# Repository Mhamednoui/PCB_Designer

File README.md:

# PCB workspace - start here

AI-assisted PCB design with KiCad. This file is the front door: it tells you which other file to
open for what you're trying to do. Don't read everything - jump to the row that matches your task.

| I want to... | Read |
|---|---|
| Understand the environment, installed tools, and what's set up | `CLAUDE.md` (auto-loaded every session) |
| See what MCP servers / Python tools / KiCad plugins exist and how to run them | `docs/TOOLING.md` |
| Build a **new** PCB project from scratch | `docs/NEW_BOARD_PLAYBOOK.md` - the **A-to-Z checklist** - then `docs/PCB_CREATION_GUIDE.md` (the tested procedure) |
| **A build failed and I need the fix** | `docs/PCB_CREATION_GUIDE.md` § "Failure catalogue" |
| Avoid mistakes already made once (KiCad 10 scripting traps, Freerouting quirks) | `docs/LESSONS_LEARNED.md` |
| Work on an **existing** project | that project's own `README.md` under `projects/<name>/` |
| **Order a board** (what the fab / price calculator asks) | that project's `MANUFACTURING.md` |
| **Check the connections without reading a PCB** | that project's `CONNECTIONS.md` - every pin, in words |
| View any board's real 3D layout + inputs/outputs in a browser | `webview/README.md` |
| **See the whole thing at a glance (pictures)** | `docs/diagrams/` — `workflow.svg`, `architecture.svg`, `status.svg` |
| **Actually run the scripts** (commands, stages, which Python) | "Running the scripts" below |

## Running the scripts

**One command does everything** (this is the normal path):
```bash
python pipeline.py uno-toggle            # full build: schematic -> place -> route -> checks -> fab files
python pipeline.py uno-toggle --list     # show which stages would run, change nothing
python pipeline.py uno-toggle --only place,route
python pipeline.py uno-toggle --skip route
```
Stages run in this order, and any that don't apply to a project are skipped automatically:

| Stage | What it does |
|---|---|
| `lint` | Design-rule lint of netlist.py (decoupling, polarity, LED resistors, shorts, pad/pin existence, registry use). Pure Python, <1 s. |
| `parts` | Registry parts vs live/cached LCSC + EasyEDA: MPN, footprint geometry, package, stock, freshness. |
| `sch` | Generate the schematic from netlist.py. |
| `sch-check` | Netlist compare (kicad-cli export vs netlist.py) plus ERC. |
| `place` | Footprints, board outline, silkscreen and pre-routed links. |
| `route` | Autoroute with Freerouting. |
| `finish` | Ground pours and stitching vias. |
| `check` | DRC including schematic parity - the gate before fab. |
| `ir` | Design IR (out/design.json): parts, nets, board geometry from netlist.py + .kicad_pcb; netlist-vs-board net cross-check; JSON-Schema validated. |
| `electrical` | Electrical rules EL-ABSMAX / EL-CONTENTION / EL-OD-PULLUP over out/design.json (runs after `ir`; NOT_JUDGED shown, never fails a hand board). |
| `review` | Design review (kicad-happy schematic/PCB/EMC analyzers + waivers.json): decoupling distance, EMC, power tree. |
| `outputs` | Gerbers, drill, BOM, CPL, STEP, schematic PDF and renders. |
| `lvs` | Independent connectivity of the fab zip itself (gerbers + drill), diffed against netlist.py. |
| `fabreport` | MANUFACTURING.md: size, layers, holes, parts, order-form answers. Read-only on the board. |
| `connections` | CONNECTIONS.md: every pin of every part and where its copper goes, in plain words. |
| `pinmap` | Firmware pin map vs netlist cross-check (enabled by a FIRMWARE block in netlist.py). |
| `spice` | Transient LTspice run of the whole board plus expected-vs-measured (enabled by a SPICE block in netlist.py). |
| `webview` | Export GLB, cache icons, build manifest, onboard to the viewer (works for any .kicad_pcb). |

Useful flags and checks: `--no-cache` (ignore the stage cache), `--describe <stage>`, `--explain RULE-ID`.
Each run writes a report to `projects/<id>/out/run/<ts>/report.html`.
```bash
python tools/ci_checks.py all
python tests/mutations/run_mutations.py --tier fast --jobs 4
python tools/parts.py            # parts registry CLI
```

`pipeline.py` **refuses to re-run design stages on a board that already has `out/fab`** — pass
`--force` if you really mean to rebuild a board that has been sent to fab.

**If you run a script directly, use KiCad's Python, not the system one:**
```bash
"C:\Program Files\KiCad\10.0\bin\python.exe" make_pcb.py place
```
Everything touching `pcbnew` (`make_sch.py`, `check_sch.py`, `make_pcb.py`, `make_outputs.py`) only
imports inside KiCad's interpreter. System `python` gives `ModuleNotFoundError: No module named
'pcbnew'`. `pipeline.py` itself runs under system Python and picks the right interpreter per stage.

The generic stages are **shared**, in `tools/boardgen/` - one copy for every board. A project's `gen/`
holds only `netlist.py` and `make_pcb.py`. Run a shared stage directly by naming the project:
```bash
"C:\Program Files\KiCad\10.0\bin\python.exe" tools/boardgen/make_sch.py blinky-555
```
KiCad's own location is resolved once in `tools/boardgen/kicad_paths.py` (set `KICAD_HOME` to override,
otherwise the newest install wins) - don't hardcode it anywhere else.

Two helpers that don't need KiCad's Python:
```bash
python tools/sym_pins.py Timer:NE555P     # a symbol's real pin numbers (follows `extends` aliases)
python tools/fp_bbox.py Package_DIP:DIP-8_W7.62mm   # a footprint's real extent around its origin
python projects/<id>/gen/netlist.py       # print the parts + nets, flagging single-pin nets
```

**The 3D platform** (details in `webview/README.md`):
```bash
python webview/server/server.py           # then open http://127.0.0.1:8787/  - Ctrl+C to stop
python webview/tools/onboard.py <id>      # add a board to the platform (GLB + icons + manifest)
```
Background services are separate processes the platform proxies at `/api/services/<name>/`. Start the
ones you want; the platform works without them:
```bash
python webview/services/drc/service.py    # DRC/ERC on demand, port 8802
python webview/services/spice/service.py  # SPICE simulation for boards with no MCU, port 8801
```

## Working offline (no internet)

**Designing and fabricating a board is 100% offline.** Simulation is the only part that isn't, and
there's a local substitute. Nothing here needs a login except Wokwi.

| Works offline | Why |
|---|---|
| KiCad + every `gen/` script, `pipeline.py` | local install, local symbol/footprint libraries |
| Freerouting autorouting | local Java app under `tools/freerouting/` |
| ERC / DRC / schematic parity | `kicad-cli`, local |
| Gerbers, drill, BOM, CPL, STEP, PDF, renders | `kicad-cli`, local |
| The webview 3D platform | server binds `127.0.0.1`; three.js is **vendored** in `webview/app/vendor/` |
| The `drc` service, `tools/sym_pins.py`, the `pinmap` stage | pure local Python |
| LTspice + the `spice` skill | local simulator |
| PlatformIO firmware builds | offline once the AVR + ESP32 toolchains are cached — they already are |

| Needs internet | Offline substitute |
|---|---|
| **Wokwi live simulation** (cloud service + metered token) | **Proteus 8** — installed on this machine. Build `firmware.hex` with PlatformIO, load it into a Proteus schematic. Note Proteus has no ESP32 model. |
| `easyeda2kicad` / LCSC part import | import the parts you need *before* going offline; they land in `projects/<id>/lib/` and stay there |
| `lcsc` / `digikey` / `mouser` / `element14` skills, datasheet fetch | cache datasheets into `projects/<id>/datasheets/` while online |

So an offline agent can do the whole board — netlist, schematic, place, route, DRC, fab files — and can
view it in the 3D platform. What it cannot do is press a button in the browser and watch real firmware
respond, because that runs on Wokwi's servers. Plan around it: **pull any external parts and datasheets
you need while you still have a connection**, since that's the only step that can't be redone later.

## Layout
```
PCB/
  CLAUDE.md          environment + status + session log (auto-loaded by Claude Code)
  README.md          this file
  docs/              workspace-wide reference (tooling, new-board playbook, lessons learned)
  webview/           generic local 3D viewer + dashboard platform for any project - see webview/ROADMAP.md
  .mcp.json          MCP server config (kicad, konnect)
  .claude/skills/    kicad-happy skills (design review, EMC, SPICE, BOM, distributors, fab prep)
  .venv/             Python tools (easyeda2kicad, skidl, kicad-skip)
  tools/boardgen/    SHARED board-generation stages used by every project
  tools/             sym_pins.py, fp_bbox.py + reference clones of external KiCad/EDA repos
  downloads/         installers (Konnect PCM, Freerouting)
  projects/          one subfolder per board - the actual work
```

## Projects
- `projects/reflex-machine/` - 10-magnet reflex/whack-a-mole game controller, Mega+ESP32 shield.
  Board design done and verified; a pre-fabrication testing pipeline is in progress.
  See `projects/reflex-machine/README.md`.
- `projects/uno-toggle/` - 2 buttons, 2 LEDs on an Arduino Uno R3 shield. Done and verified, including
  live simulation in the webview. The simplest worked example of the full pipeline.
  See `projects/uno-toggle/README.md`.
- `projects/blinky-555/` - standalone NE555 1 Hz LED flasher, 70x45 mm, 2-layer through-hole. Built as the
  pipeline's test case for a board with **no MCU** (own outline, own mounting holes, real VCC rail).
  0 errors / 0 unconnected / 0 parity. **Simulated in the webview with LTspice** (1.385 Hz, as designed).
  See `projects/blinky-555/README.md`.
- `projects/pic-programmer/` - **not ours.** KiCad's own demo board, kept as the regression test that the
  webview platform works for any project. See its README.

## Working style
Small steps, low token use: do one thing, show the result, ask before the next. Never hand-edit
generated KiCad files - fix the generating script instead.

## Capturing what you learn
Write down anything non-obvious as soon as you find it, at the level it belongs:
- **A trap that could bite the next board** (KiCad API quirk, tool install gotcha, a script bug and its fix) ->
  `docs/LESSONS_LEARNED.md`.
- **A finding specific to one pipeline stage** (a test result, a measured value, why an approach was
  dropped) -> that stage's own file, e.g. `projects/<name>/test/<stage>/REPORT.md`.
- **A decision or open question specific to one project** -> that project's `HANDOVER.md`.
- **Anything that changes the workspace setup or a project's status** -> `CLAUDE.md` status + session log.
Keep it terse and factual - the goal is that a fresh session picks up exactly where you left off
without re-deriving what you already figured out.

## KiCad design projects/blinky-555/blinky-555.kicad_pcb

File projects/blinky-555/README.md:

# Blinky 555 — 1 Hz LED flasher

**Ordering it:** everything a fab or price calculator asks (size in cm, layers, holes, parts, order-form answers) is in [`MANUFACTURING.md`](MANUFACTURING.md) - generated from the real board, regenerate with `python pipeline.py blinky-555 --only fabreport`.
**Checking the wiring without reading a PCB:** [`CONNECTIONS.md`](CONNECTIONS.md) lists every pin of every part and where it goes, in words.

A standalone NE555 astable that blinks one LED at about 1.4 Hz from a 9–12 V supply.
70 × 45 mm, 2-layer, entirely through-hole, 9 parts.

**Status: done.** `0 DRC errors / 0 unconnected / 0 schematic-parity / 3 silk warnings`, ERC clean,
netlist compare 0 mismatches. Fab files in `out/fab`, documentation and renders in `out/docs`.

## Why this board exists

It is the pipeline's **test case for a board with no microcontroller**. The other two boards are
Arduino shields, which hide several things this one is forced to do for itself:

- pick its **own board outline** (a rectangle) instead of inheriting one from a shield footprint
- place its **own mounting holes**
- carry a **real VCC rail**, so two power-flag nets rather than just GND
- use a **multi-pin DIP** part, so pin numbers must come from the symbol, not from 1/2 convention
- use only **stock KiCad libraries** — `PROJECT_LIBS` is empty, nothing is vendored into `lib/`

Building it found six real bugs, all written up in `docs/PCB_CREATION_GUIDE.md`. Three of the fixes
were to the shared generator scripts and benefit every future board:

| Fix | Effect |
|---|---|
| silk text offset derived from the footprint courtyard instead of a fixed 2.2 mm | 60 → 3 silk warnings |
| `make_sch.py` no longer copies `ki_fp_filters` / `ki_locked` onto placed symbols | 9 → 0 parity warnings |
| `make_outputs.py` derives the gerber layer list from the board | a 4-layer board no longer ships with no inner copper |

## Circuit

Standard 555 astable. `f ≈ 1.44 / ((R1 + 2·R2)·C1) = 1.44 / ((10k + 94k)·10 µF) ≈ 1.4 Hz`.

| Part | Value | Role |
|---|---|---|
| U1 | NE555P (DIP-8) | the timer |
| R1 | 10 k | VCC → DISCH (charge path) |
| R2 | 47 k | DISCH → TRIG (charge and discharge path) |
| C1 | 10 µF electrolytic | timing capacitor — **polarity matters**, pad 1 (left) is + |
| C2 | 10 nF | noise filter on CONT |
| C3 | 100 nF | decoupling at U1 pin 8 |
| R3 | 470 R | LED current limit (~15 mA at 9 V) |
| D1 | red LED, 5 mm | the output |
| J1 | 2-pin terminal block | 9–12 V in — **polarity marked on the silkscreen**, + is pad 1 |

`U1` pin 4 (`~RST`) is tied to VCC. A floating reset pin holds the timer in reset at random and is
the most common reason a hand-wired 555 does nothing.

## Simulate it
No microcontroller means nothing for Wokwi to run, so this board is simulated with **LTspice** on its
own netlist (`SPICE` block in `gen/netlist.py`, run by `tools/boardgen/make_spice.py`):

| | Hand calculation | LTspice |
|---|---|---|
| frequency | 1.39 Hz | **1.385 Hz** |
| LED on / off | 395 / 326 ms | **395.4 / 326.5 ms** (54.8 % duty) |
| LED current | ~15 mA at 9 V | **14.8 mA** at 9 V, 21.1 mA at 12 V |

```bash
python pipeline.py blinky-555 --only spice          # or: python tools/boardgen/make_spice.py blinky-555 --set VCC=12
```
**In the webview**: start `webview/server/server.py` and `webview/services/spice/service.py`, pick
blinky-555, press **Run SPICE**. D1 blinks on the 3D board in real time, C1's voltage ticks live, and the
Analyzer tab shows the waveforms. The supply slider (9-12 V) sets the next run. Offline, no quota.

## Build it

```bash
python pipeline.py blinky-555 --list     # confirm the stages
python pipeline.py blinky-555 --force    # --force because out/fab already exists
```

Everything comes from `gen/netlist.py`. **Never hand-edit the generated KiCad files** — change the
generator and re-run. See the workspace `README.md` § "Running the scripts".

## Assembly notes

Two parts can be fitted the wrong way round and both are marked on the silkscreen — check them:
- **C1** — the electrolytic. `C1+` is printed beside it; the positive lead goes in pad 1.
- **J1** — `+` and `-` are printed above the two pads. Reversing the supply destroys the 555.

The LED and the 555 itself are also polarised (cathode flat / pin-1 notch), marked by the footprints'
own silkscreen.

## Reverse-polarity diode (P2-T7b)
J1 now feeds the board through a series 1N4007 (D2): VIN -> D2 -> VCC. A reversed adapter no longer reaches the 555. The drop (about 0.7 V at 15 mA) leaves ~8.3 V at the worst case (9 V in), well inside the NE555's 4.5-16 V range; the LED current at 9 V fell to 13.3 mA (SPICE). The fuse and TVS findings of EL-CONN-PROT are waived in `waivers.json` with reasons (50 mA load, battery or bench supply, short lead).

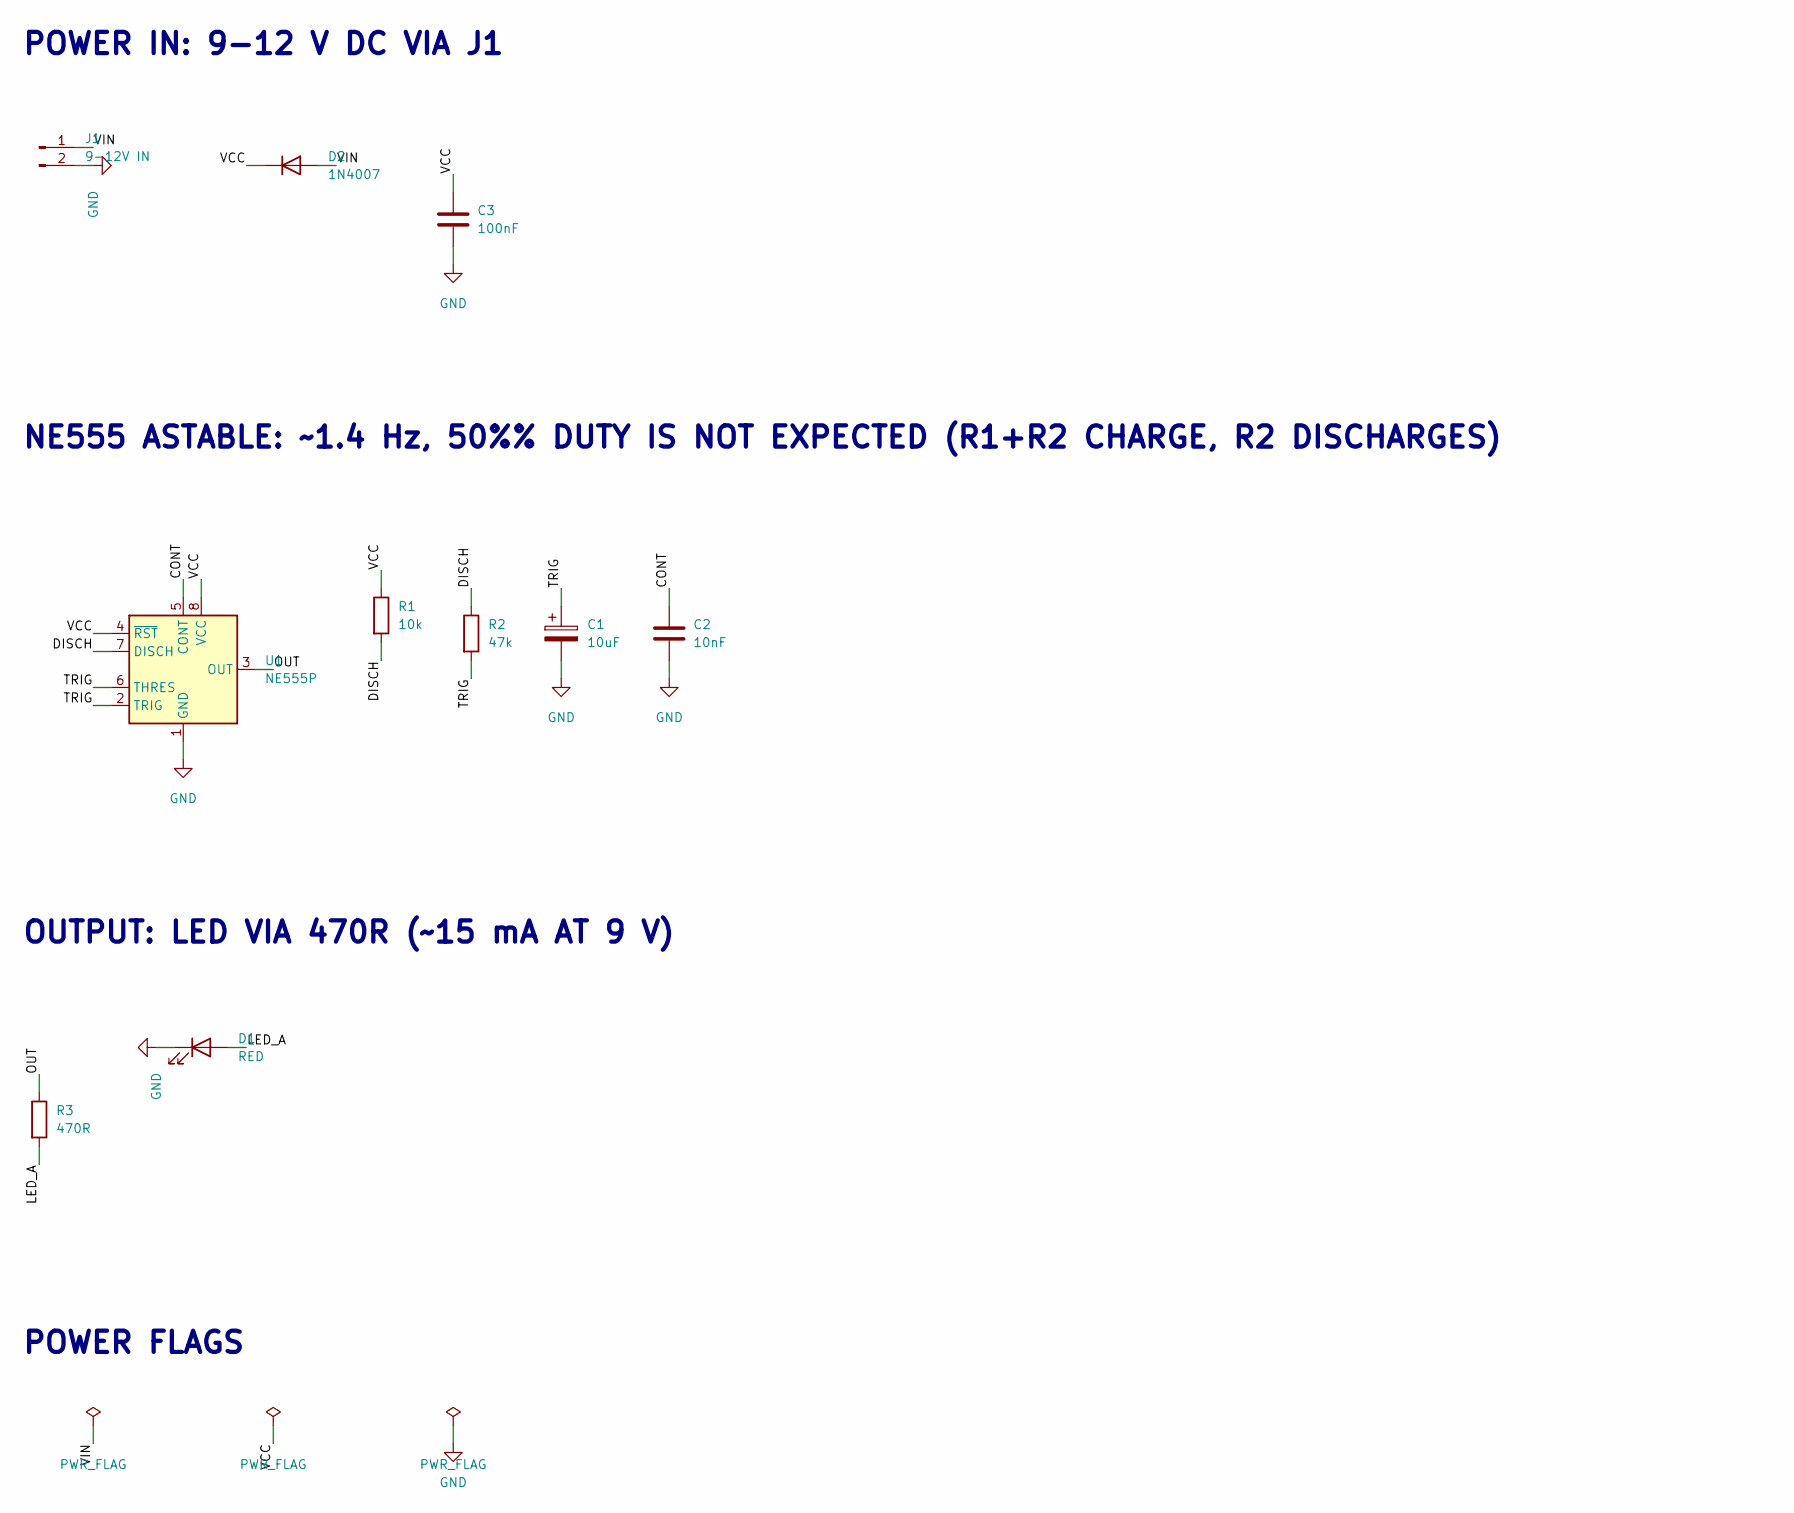
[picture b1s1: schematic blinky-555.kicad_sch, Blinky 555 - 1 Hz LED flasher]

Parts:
C1: 10uF; CP_Radial_D6.3mm_P2.50mm
C2: 10nF; C_Disc_D5.0mm_W2.5mm_P5.00mm
C3: 100nF; C_Disc_D5.0mm_W2.5mm_P5.00mm
D1: RED; LED_D5.0mm; LCSC C2895470
D2: 1N4007; D_DO-41_SOD81_P7.62mm_Horizontal
J1: 9-12V IN; TerminalBlock_MaiXu_MX126-5.0-02P_1x02_P5.00mm
R1: 10k; R_Axial_DIN0207_L6.3mm_D2.5mm_P10.16mm_Horizontal
R2: 47k; R_Axial_DIN0207_L6.3mm_D2.5mm_P10.16mm_Horizontal
R3: 470R; R_Axial_DIN0207_L6.3mm_D2.5mm_P10.16mm_Horizontal
U1: NE555P; DIP-8_W7.62mm

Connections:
/CONT: C2.1, U1.5 (CONT)
/DISCH: R1.2, R2.1, U1.7 (DISCH)
/LED_A: D1.2 (A), R3.2
/OUT: R3.1, U1.3 (OUT)
/TRIG: C1.1, R2.2, U1.2 (TRIG), U1.6 (THRES)
/VCC: C3.1, D2.1 (K), R1.1, U1.4 (~RST), U1.8 (VCC)
/VIN: D2.2 (A), J1.1
GND: C1.2, C2.2, C3.2, D1.1 (K), J1.2, U1.1 (GND)

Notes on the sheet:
POWER IN: 9-12 V DC VIA J1
NE555 ASTABLE: ~1.4 Hz, 50%% DUTY IS NOT EXPECTED (R1+R2 CHARGE, R2 DISCHARGES)
OUTPUT: LED VIA 470R (~15 mA AT 9 V)
POWER FLAGS

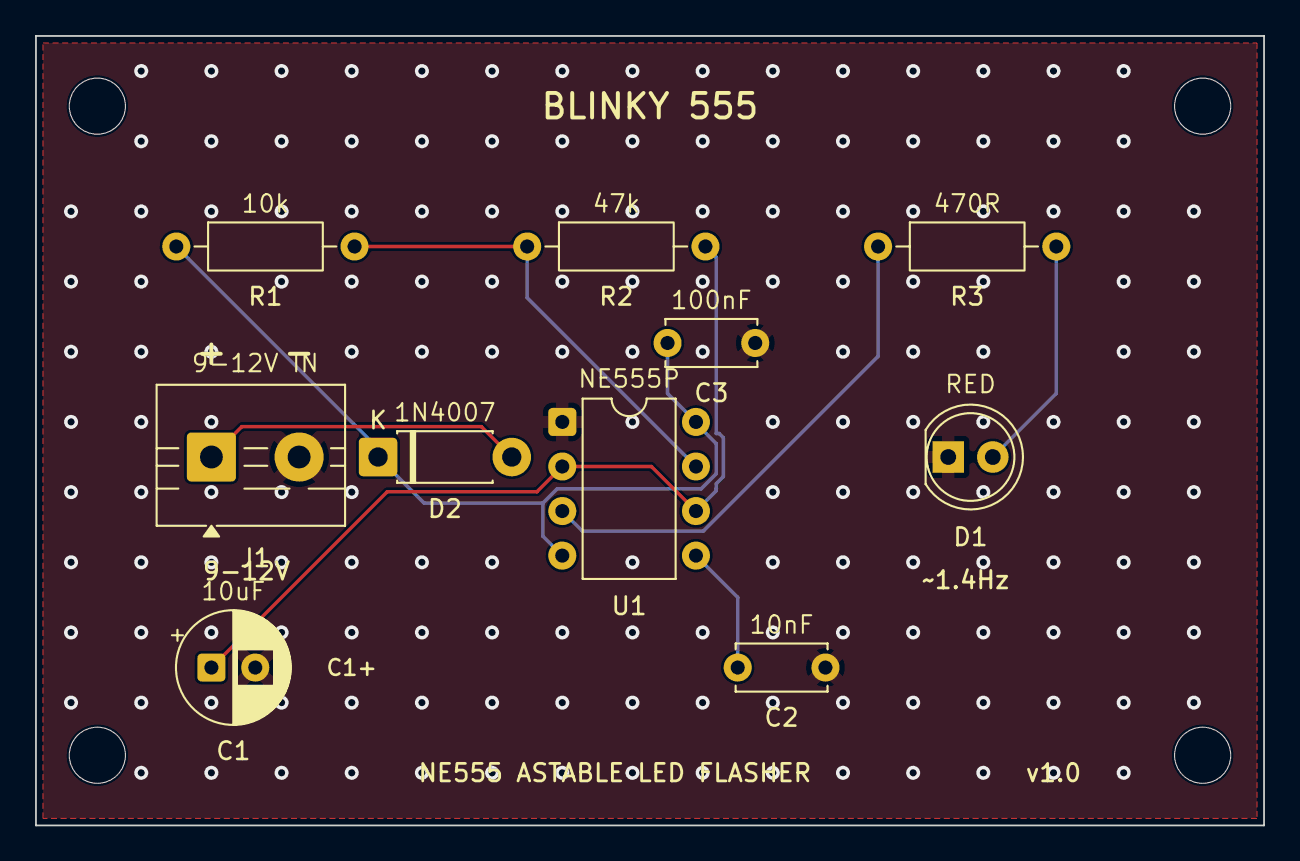
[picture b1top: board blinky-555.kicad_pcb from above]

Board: 2 copper layers, 70.0 x 45.0 mm, 14 parts (0 on the bottom side), 8 nets.

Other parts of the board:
H1, H2, H3, H4: MountingHole_3.2mm_M3

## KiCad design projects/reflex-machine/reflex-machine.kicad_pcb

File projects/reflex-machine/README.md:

# Reflex Machine PCB - start here

**Ordering it:** everything a fab or price calculator asks (size in cm, layers, holes, parts, order-form answers) is in [`MANUFACTURING.md`](MANUFACTURING.md) - generated from the real board, regenerate with `python pipeline.py reflex-machine --only fabreport`.
**Checking the wiring without reading a PCB:** [`CONNECTIONS.md`](CONNECTIONS.md) lists every pin of every part and where it goes, in words.

10-electromagnet reflex/whack-a-mole game controller. Arduino Mega 2560 (shield-mounted) +
ESP32 DevKit V1, all through-hole parts. This file tells you which other file to open next -
don't read everything.

| I want to... | Read |
|---|---|
| Know what's done, what's pending, and open questions | `HANDOVER.md` |
| See the full build history and how it was made | `PROJECT_LOG.md` |
| See the original spec and design decisions | `DESIGN_BRIEF.md` |
| Wire up the physical machine | `WIRING_GUIDE.md` |
| Regenerate or change the board (schematic/PCB scripts) | `gen/` - see `docs/NEW_BOARD_PLAYBOOK.md` in the workspace root |
| Test the design before/after fabrication | `test/README.md` |

## Status (2026-09-17)
Board is **done and verified**: 160x125mm, 2-layer, ERC clean, DRC 0 errors/0 unconnected/0 parity.
Fab files in `out/fab/`, docs+renders+STEP in `out/docs/`.

A pre-fabrication **testing pipeline** is in progress (see `test/README.md`):
1. Electrical check on the real PCB file (DRC/ERC, power/signal integrity, per-magnet trace current) - **done, pass**.
2. SPICE simulation of the analog subcircuits (debounce filters, coin optocoupler, level-shifter) - **done**,
   via LTspice - 9/9 filters confirmed within 0.3% of calculated values. See `test/spice/REPORT.md`.
3. Functional/logic simulation (Wokwi) - **input wiring confirmed** (S1/S2/S3/RST/coin each pull the
   correct Mega pin, verified with a real scripted scenario against the real firmware). Full game-round
   logic not yet checked (costs simulation minutes). See `test/wokwi/README.md` and `test/wokwi/USAGE_LOG.md`.
4. Physical bring-up self-test - **ready** (`test/bringup/`), usable once the board is manufactured.

Open questions for the user: real magnet current/coil resistance (now step 3 of the bring-up checklist),
ESP32 row pitch (25.4mm assumed).

## Folder layout
```
reflex-machine.kicad_sch / .kicad_pcb   the design (open in KiCad)
HANDOVER.md          current state, pending decisions - read first
PROJECT_LOG.md        full build history, part-by-part
DESIGN_BRIEF.md       spec + decisions made before designing
WIRING_GUIDE.md        user-facing wiring instructions
gen/                  scripts that generate the schematic/PCB from netlist.py (source of truth)
sim/                  PlatformIO projects to build real firmware.hex for the Mega/ESP32
test/                 pre-fabrication testing pipeline (see test/README.md)
analysis/             cached kicad-happy analyzer output
out/fab/              gerbers, BOM, CPL for JLCPCB
out/docs/             STEP, schematic PDF, renders, full BOM
```

## Known deviation from the brief: reverse-polarity protection
DESIGN_BRIEF (section on the 12 V input) promised a P-MOSFET reverse-polarity stage. The board as built has none.
The protection is the P6KE15A TVS (D1) across `+12V` behind the 10 A blade fuse F1: a reversed supply forward-biases D1
and blows the fuse (a crowbar). That is cheaper and survives, but it destroys a fuse on every wrong-way connection and
the 10 A fuse is slow against a 1.5 A-per-channel load. Found by EL-CONN-PROT (P2-T7); not changed.

## Known limit: total magnet current (EL-BUDGET, waived until 2027-04-30)
All 10 coils on at their 1.5 A design figure is 15 A on `+12V`, over the 10 A fuse F1 and the 10 A copper rating.
DESIGN_BRIEF B2 sizes the board for 10 A TOTAL; an overload blows F1 before the copper is stressed (fails safe).
Firmware PWM_ON=100/255 averages ~5.9 A with all on, but it is runtime-settable, so it is not relied on.
Measure the real coil current at bring-up (step 3) and re-judge; the waiver is in `waivers.json`.

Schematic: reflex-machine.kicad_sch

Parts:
A1: Arduino Mega 2560 R3; Arduino_Mega2560_R3_Shield
A2: ESP32 DevKit V1 (30 pin); ESP32_DevKit_V1_30pin_Socket
C1: 1000uF 25V; CP_Radial_D10.0mm_P5.00mm; LCSC C48935382
C2, C6: 220uF 25V; CP_Radial_D6.3mm_P2.50mm; LCSC C47344177
C3, C7, C9, C10, C11, C12, C13: 100nF; C_Disc_D5.0mm_W2.5mm_P5.00mm
C8: 1nF; C_Disc_D5.0mm_W2.5mm_P5.00mm; LCSC C49002957
D1: P6KE15A; D_DO-15_P10.16mm_Horizontal; LCSC C294003
D2: 1N4007; D_DO-41_SOD81_P7.62mm_Horizontal; LCSC C2985028
D3, D4: GREEN; LED_D5.0mm
D11, D12, D13, D14, D15, D16, D17, D18, D19, D20: 1N5822; D_DO-201AD_P5.08mm_Vertical_CathodeUp; LCSC C2476
D21, D22, D23, D24, D25, D26, D27, D28, D29, D30: RED; LED_D3.0mm; LCSC C2895470
F1: 10A mini blade; Fuseholder_Blade_Mini_Keystone_3568
J1: 12V_IN; TerminalBlock_Phoenix_MKDS-3-2-5.08_1x02_P5.08mm_Horizontal
J2: MAG1; TerminalBlock_Phoenix_MKDS-1,5-2-5.08_1x02_P5.08mm_Horizont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
J3: MAG2; TerminalBlock_Phoenix_MKDS-1,5-2-5.08_1x02_P5.08mm_Horizont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
J4: MAG3; TerminalBlock_Phoenix_MKDS-1,5-2-5.08_1x02_P5.08mm_Horizont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
J5: MAG4; TerminalBlock_Phoenix_MKDS-1,5-2-5.08_1x02_P5.08mm_Horizont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
J6: MAG5; TerminalBlock_Phoenix_MKDS-1,5-2-5.08_1x02_P5.08mm_Horizont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
J7: MAG6; TerminalBlock_Phoenix_MKDS-1,5-2-5.08_1x02_P5.08mm_Horizont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
J8: MAG7; TerminalBlock_Phoenix_MKDS-1,5-2-5.08_1x02_P5.08mm_Horizont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
J9: MAG8; TerminalBlock_Phoenix_MKDS-1,5-2-5.08_1x02_P5.08mm_Horizont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
J10: MAG9; TerminalBlock_Phoenix_MKDS-1,5-2-5.08_1x02_P5.08mm_Horizont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
J11: MAG10; TerminalBlock_Phoenix_MKDS-1,5-2-5.08_1x02_P5.08mm_Horizont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
J12: COIN; TerminalBlock_Phoenix_PT-1,5-3-3.5-H_1x03_P3.50mm_Horizontal
J13: BUTTONS; TerminalBlock_Phoenix_PT-1,5-8-3.5-H_1x08_P3.50mm_Horizontal
J14: STATUS_LEDS; TerminalBlock_Phoenix_PT-1,5-8-3.5-H_1x08_P3.50mm_Horizontal
J15: 7SEG; TerminalBlock_Phoenix_PT-1,5-8-3.5-H_1x08_P3.50mm_Horizontal
J16: MEGA SPARE; PinHeader_2x10_P2.54mm_Vertical
J17: ESP32 SPARE; PinHeader_2x04_P2.54mm_Vertical
Q1, Q2, Q3, Q4, Q5, Q6, Q7, Q8, Q9, Q10: IRLZ44N; TO-220-3_Vertical; LCSC C38774
R1: 4.7k; R_Axial_DIN0207_L6.3mm_D2.5mm_P10.16mm_Horizontal
R2, R43, R44, R45, R46, R62: 1k; R_Axial_DIN0207_L6.3mm_D2.5mm_P10.16mm_Horizontal
R11, R12, R13, R14, R15, R16, R17, R18, R19, R20: 100R; R_Axial_DIN0207_L6.3mm_D2.5mm_P10.16mm_Horizontal
R21, R22, R23, R24, R25, R26, R27, R28, R29, R30, R42, R47, R48, R49, R50: 10k; R_Axial_DIN0207_L6.3mm_D2.5mm_P10.16mm_Horizontal; LCSC C2649453
R31, R32, R33, R34, R35, R36, R37, R38, R39, R40, R41: 2.2k; R_Axial_DIN0207_L6.3mm_D2.5mm_P10.16mm_Horizontal
R51, R52, R53, R54: 330R; R_Axial_DIN0207_L6.3mm_D2.5mm_P10.16mm_Horizontal
R55, R56, R57, R58, R59, R60, R61: 470R; R_Axial_DIN0207_L6.3mm_D2.5mm_P10.16mm_Horizontal
R63: 2k; R_Axial_DIN0207_L6.3mm_D2.5mm_P10.16mm_Horizontal
U1: 5V 2A module (K7805-2000R3); Converter_DCDC_RECOM_R-78B-2.0_THT; LCSC C18212380
U2: PC817; DIP-4_W7.62mm; LCSC C20612594
U3: 74HC595N; DIP-16_W7.62mm; LCSC C507175

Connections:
+3V3: A1.3V3 (3.3V), J16.3
+5V: A1.5V1 (5V), A1.5V3 (5V), A1.5V4 (5V), A2.15 (VIN(5V)), C6.1, C7.1, C13.1, J16.1, R2.1, R42.1, R47.1, R48.1, R49.1, R50.1, U1.3 (OUT), U3.10 (~SRCLR), U3.16 (VCC)
+12V: C1.1, D1.1 (K), D2.2 (A), D11.1 (K), D12.1 (K), D13.1 (K), D14.1 (K), D15.1 (K), D16.1 (K), D17.1 (K), D18.1 (K), D19.1 (K), D20.1 (K), D21.2 (A), D22.2 (A), D23.2 (A), D24.2 (A), D25.2 (A), D26.2 (A), D27.2 (A), D28.2 (A), D29.2 (A), D30.2 (A), F1.2, J2.1, J3.1, J4.1, J5.1, J6.1, J7.1, J8.1, J9.1, J10.1, J11.1, J12.1, R1.1, R41.1
/+3V3_ESP: A2.30 (3V3), J17.1
/+12V_IN: F1.1, J1.1
/+12V_REG: C2.1, C3.1, D2.1 (K), U1.1 (IN)
/BTN_RST: A1.D28, C12.1, R46.2, R50.2
/BTN_RST_EXT: J13.7, R46.1
/BTN_S1: A1.D22, C9.1, R43.2, R47.2
/BTN_S1_EXT: J13.1, R43.1
/BTN_S2: A1.D24, C10.1, R44.2, R48.2
/BTN_S2_EXT: J13.3, R44.1
/BTN_S3: A1.D26, C11.1, R45.2, R49.2
/BTN_S3_EXT: J13.5, R45.1
/COIN_IN: A1.D2 (D2_INT0), C8.1, R42.2, U2.4
/COIN_OPTO_A: R41.2, U2.1
/COIN_SIG: J12.3, U2.2
/ESP_IO14: A2.11 (IO14), J17.8
/ESP_IO25: A2.8 (IO25), J17.3
/ESP_IO26: A2.9 (IO26), J17.4
/ESP_IO27: A2.10 (IO27), J17.5
/ESP_IO32: A2.6 (IO32), J17.6
/ESP_IO33: A2.7 (IO33), J17.7
/ESP_RX2: A2.25 (RX2/IO16), R62.2, R63.1
/ESP_TX2: A1.D19 (D19/RX1), A2.24 (TX2/IO17)
/I2C_SCL: A1.D21 (D21/SCL), J16.6
/I2C_SDA: A1.D20 (D20/SDA), J16.5
/LED1: A1.A3, R51.1
/LED1_OUT: J14.1, R51.2
/LED2: A1.A4, R52.1
/LED2_OUT: J14.3, R52.2
/LED3: A1.A5, R53.1
/LED3_OUT: J14.5, R53.2
/LED4: A1.A6, R54.1
/LED4_OUT: J14.7, R54.2
/MAG1_G: Q1.1 (G), R11.2, R21.1
/MAG1_LED: D21.1 (K), R31.1
/MAG1_OUT: D11.2 (A), J2.2, Q1.2 (D), R31.2
/MAG1_PWM: A1.D3 (D3_INT1), R11.1
/MAG2_G: Q2.1 (G), R12.2, R22.1
/MAG2_LED: D22.1 (K), R32.1
/MAG2_OUT: D12.2 (A), J3.2, Q2.2 (D), R32.2
/MAG2_PWM: A1.D5, R12.1
/MAG3_G: Q3.1 (G), R13.2, R23.1
/MAG3_LED: D23.1 (K), R33.1
/MAG3_OUT: D13.2 (A), J4.2, Q3.2 (D), R33.2
/MAG3_PWM: A1.D6, R13.1
/MAG4_G: Q4.1 (G), R14.2, R24.1
/MAG4_LED: D24.1 (K), R34.1
/MAG4_OUT: D14.2 (A), J5.2, Q4.2 (D), R34.2
/MAG4_PWM: A1.D7, R14.1
/MAG5_G: Q5.1 (G), R15.2, R25.1
/MAG5_LED: D25.1 (K), R35.1
/MAG5_OUT: D15.2 (A), J6.2, Q5.2 (D), R35.2
/MAG5_PWM: A1.D8, R15.1
/MAG6_G: Q6.1 (G), R16.2, R26.1
/MAG6_LED: D26.1 (K), R36.1
/MAG6_OUT: D16.2 (A), J7.2, Q6.2 (D), R36.2
/MAG6_PWM: A1.D9, R16.1
/MAG7_G: Q7.1 (G), R17.2, R27.1
/MAG7_LED: D27.1 (K), R37.1
/MAG7_OUT: D17.2 (A), J8.2, Q7.2 (D), R37.2
/MAG7_PWM: A1.D10, R17.1
/MAG8_G: Q8.1 (G), R18.2, R28.1
/MAG8_LED: D28.1 (K), R38.1
/MAG8_OUT: D18.2 (A), J9.2, Q8.2 (D), R38.2
/MAG8_PWM: A1.D11, R18.1
/MAG9_G: Q9.1 (G), R19.2, R29.1
/MAG9_LED: D29.1 (K), R39.1
/MAG9_OUT: D19.2 (A), J10.2, Q9.2 (D), R39.2
/MAG9_PWM: A1.D12, R19.1
/MAG10_G: Q10.1 (G), R20.2, R30.1
/MAG10_LED: D30.1 (K), R40.1
/MAG10_OUT: D20.2 (A), J11.2, Q10.2 (D), R40.2
/MAG10_PWM: A1.D44, R20.1
/MEGA_TX1: A1.D18 (D18/TX1), R62.1
/PWR5_LED: D4.2 (A), R2.2
/PWR12_LED: D3.2 (A), R1.2
/SEG_A: J15.1, R55.2
/SEG_B: J15.2, R56.2
/SEG_C: J15.3, R57.2
/SEG_CLOCK: A1.A2, U3.11 (SRCLK)
/SEG_D: J15.4, R58.2
/SEG_DATA: A1.A0, U3.14 (SER)
/SEG_E: J15.5, R59.2
/SEG_F: J15.6, R60.2
/SEG_G: J15.7, R61.2
/SEG_LATCH: A1.A1, U3.12 (RCLK)
/SEG_QB: R61.1, U3.1 (QB)
/SEG_QC: R60.1, U3.2 (QC)
/SEG_QD: R55.1, U3.3 (QD)
/SEG_QE: R59.1, U3.4 (QE)
/SEG_QF: R57.1, U3.5 (QF)
/SEG_QG: R56.1, U3.6 (QG)
/SEG_QH: R58.1, U3.7 (QH)
/SPARE_A7: A1.A7, J16.15
/SPARE_A8: A1.A8, J16.16
/SPARE_CS: A1.D53 (D53_CS), J16.20
/SPARE_D4: A1.D4, J16.9
/SPARE_D13: A1.D13, J16.10
/SPARE_D30: A1.D30, J16.11
/SPARE_D31: A1.D31, J16.12
/SPARE_D32: A1.D32, J16.13
/SPARE_D33: A1.D33, J16.14
/SPARE_MISO: A1.D50 (D50_MISO), J16.18
/SPARE_MOSI: A1.D51 (D51_MOSI), J16.19
/SPARE_RX3: A1.D15 (D15/RX3), J16.8
/SPARE_SCK: A1.D52 (D52_SCK), J16.17
/SPARE_TX3: A1.D14 (D14/TX3), J16.7
GND: A1.GND1 (GND), A1.GND2 (GND), A1.GND3 (GND), A1.GND5 (GND), A1.GND6 (GND), A2.14 (GND), A2.29 (GND), C1.2, C2.2, C3.2, C6.2, C7.2, C8.2, C9.2, C10.2, C11.2, C12.2, C13.2, D1.2 (A), D3.1 (K), D4.1 (K), J1.2, J12.2, J13.2, J13.4, J13.6, J13.8, J14.2, J14.4, J14.6, J14.8, J15.8, J16.2, J16.4, J17.2, Q1.3 (S), Q2.3 (S), Q3.3 (S), Q4.3 (S), Q5.3 (S), Q6.3 (S), Q7.3 (S), Q8.3 (S), Q9.3 (S), Q10.3 (S), R21.2, R22.2, R23.2, R24.2, R25.2, R26.2, R27.2, R28.2, R29.2, R30.2, R63.2, U1.2 (GND), U2.3, U3.8 (GND), U3.13 (~OE)

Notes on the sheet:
POWER: 12V INPUT, FUSE, SURGE PROTECTION, 12V -> 5V REGULATOR
CONTROLLERS: ARDUINO MEGA 2560 (shield) + ESP32 DEVKIT V1
SERIAL: MEGA TX1 (5V) -> DIVIDER -> ESP32 RX2 (3.3V)
10x ELECTROMAGNET DRIVERS (IRLZ44N + FLYBACK DIODE + ON LED)
COIN ACCEPTOR INPUT (OPTOCOUPLER)
BUTTONS: SPEED1 / SPEED2 / SPEED3 / RESET
STATUS LEDS
7-SEGMENT DISPLAY DRIVER (74HC595)
EXPANSION HEADER
POWER FLAGS

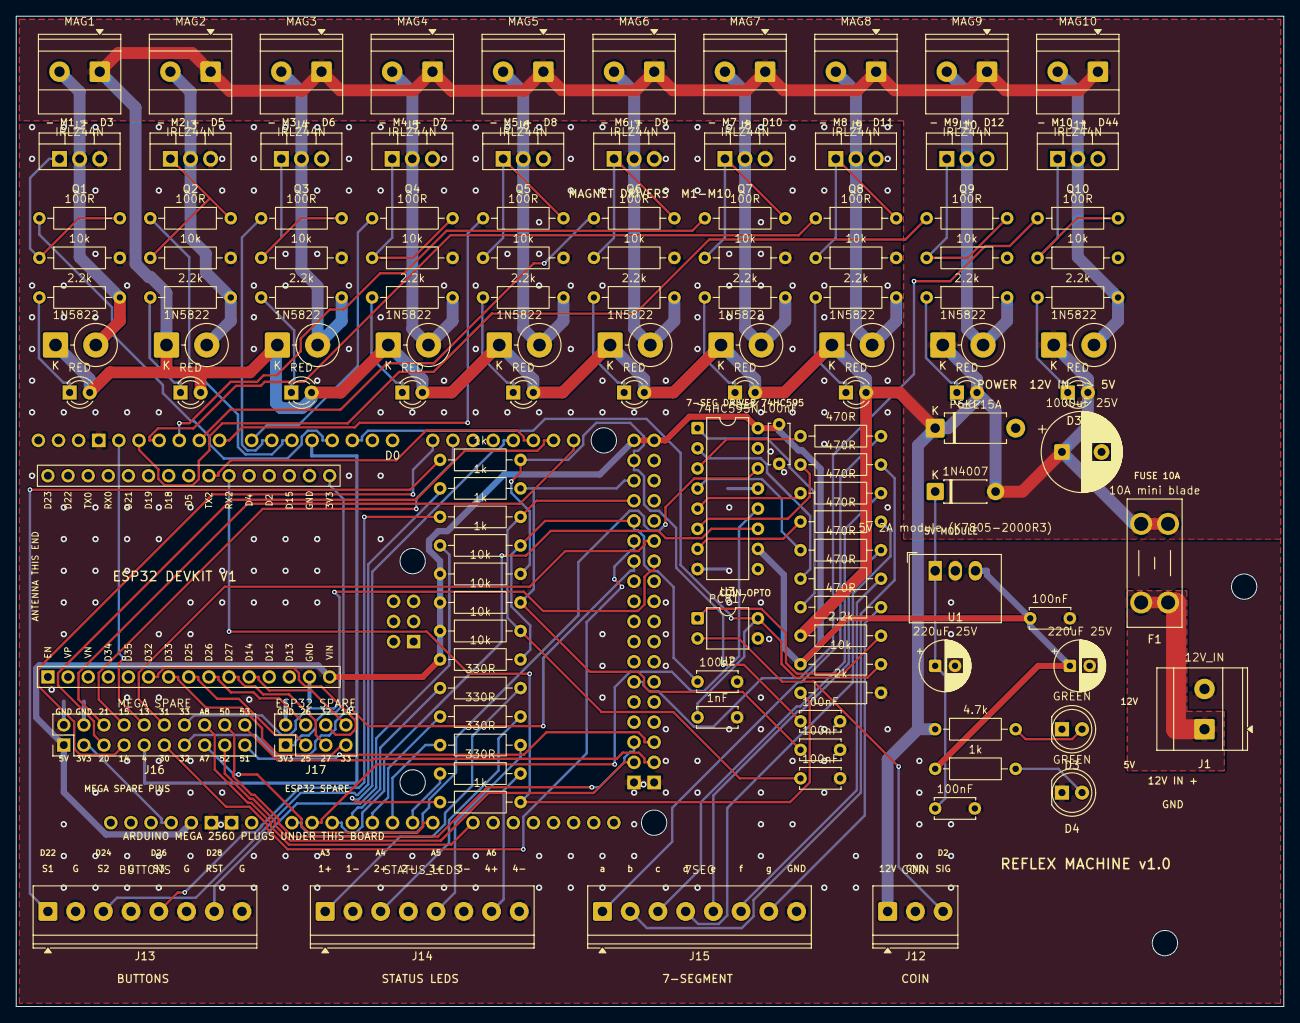
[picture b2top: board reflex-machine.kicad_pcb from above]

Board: 2 copper layers, 160.0 x 125.0 mm, 125 parts (0 on the bottom side), 110 nets.

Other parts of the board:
H1, H2: MountingHole_3.2mm_M3

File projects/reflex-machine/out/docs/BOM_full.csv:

Qty,Value,Designators,Footprint,LCSC,Assembly
1,Arduino Mega 2560 R3,A1,Arduino_Mega2560_R3_Shield,,hand solder / plug-in
1,ESP32 DevKit V1 (30 pin),A2,ESP32_DevKit_V1_30pin_Socket,,hand solder / plug-in
1,1000uF 25V,C1,CP_Radial_D10.0mm_P5.00mm,C48935382,hand solder / plug-in
2,220uF 25V,"C2,C6",CP_Radial_D6.3mm_P2.50mm,C47344177,hand solder / plug-in
7,100nF,"C3,C7,C9,C10,C11,C12,C13",C_Disc_D5.0mm_W2.5mm_P5.00mm,,hand solder / plug-in
1,1nF,C8,C_Disc_D5.0mm_W2.5mm_P5.00mm,C49002957,hand solder / plug-in
1,P6KE15A,D1,D_DO-15_P10.16mm_Horizontal,C294003,hand solder / plug-in
1,1N4007,D2,D_DO-41_SOD81_P7.62mm_Horizontal,C2985028,hand solder / plug-in
2,GREEN,"D3,D4",LED_D5.0mm,,hand solder / plug-in
10,1N5822,"D11,D12,D13,D14,D15,D16,D17,D18,D19,D20",D_DO-201AD_P5.08mm_Vertical_CathodeUp,C2476,hand solder / plug-in
10,RED,"D21,D22,D23,D24,D25,D26,D27,D28,D29,D30",LED_D3.0mm,C2895470,hand solder / plug-in
1,10A mini blade,F1,Fuseholder_Blade_Mini_Keystone_3568,,hand solder / plug-in
1,12V_IN,J1,TerminalBlock_Phoenix_MKDS-3-2-5.08_1x02_P5.08mm_Horizontal,,hand solder / plug-in
1,MAG1,J2,"TerminalBlock_Phoenix_MKDS-1,5-2-5.08_1x02_P5.08mm_Horizontal",,hand solder / plug-in
1,MAG2,J3,"TerminalBlock_Phoenix_MKDS-1,5-2-5.08_1x02_P5.08mm_Horizontal",,hand solder / plug-in
1,MAG3,J4,"TerminalBlock_Phoenix_MKDS-1,5-2-5.08_1x02_P5.08mm_Horizontal",,hand solder / plug-in
1,MAG4,J5,"TerminalBlock_Phoenix_MKDS-1,5-2-5.08_1x02_P5.08mm_Horizontal",,hand solder / plug-in
1,MAG5,J6,"TerminalBlock_Phoenix_MKDS-1,5-2-5.08_1x02_P5.08mm_Horizontal",,hand solder / plug-in
1,MAG6,J7,"TerminalBlock_Phoenix_MKDS-1,5-2-5.08_1x02_P5.08mm_Horizontal",,hand solder / plug-in
1,MAG7,J8,"TerminalBlock_Phoenix_MKDS-1,5-2-5.08_1x02_P5.08mm_Horizontal",,hand solder / plug-in
1,MAG8,J9,"TerminalBlock_Phoenix_MKDS-1,5-2-5.08_1x02_P5.08mm_Horizontal",,hand solder / plug-in
1,MAG9,J10,"TerminalBlock_Phoenix_MKDS-1,5-2-5.08_1x02_P5.08mm_Horizontal",,hand solder / plug-in
1,MAG10,J11,"TerminalBlock_Phoenix_MKDS-1,5-2-5.08_1x02_P5.08mm_Horizontal",,hand solder / plug-in
1,COIN,J12,"TerminalBlock_Phoenix_PT-1,5-3-3.5-H_1x03_P3.50mm_Horizontal",,hand solder / plug-in
1,BUTTONS,J13,"TerminalBlock_Phoenix_PT-1,5-8-3.5-H_1x08_P3.50mm_Horizontal",,hand solder / plug-in
1,STATUS_LEDS,J14,"TerminalBlock_Phoenix_PT-1,5-8-3.5-H_1x08_P3.50mm_Horizontal",,hand solder / plug-in
1,7SEG,J15,"TerminalBlock_Phoenix_PT-1,5-8-3.5-H_1x08_P3.50mm_Horizontal",,hand solder / plug-in
1,MEGA SPARE,J16,PinHeader_2x10_P2.54mm_Vertical,,hand solder / plug-in
1,ESP32 SPARE,J17,PinHeader_2x04_P2.54mm_Vertical,,hand solder / plug-in
10,IRLZ44N,"Q1,Q2,Q3,Q4,Q5,Q6,Q7,Q8,Q9,Q10",TO-220-3_Vertical,C38774,hand solder / plug-in
1,4.7k,R1,R_Axial_DIN0207_L6.3mm_D2.5mm_P10.16mm_Horizontal,,hand solder / plug-in
6,1k,"R2,R43,R44,R45,R46,R62",R_Axial_DIN0207_L6.3mm_D2.5mm_P10.16mm_Horizontal,,hand solder / plug-in
10,100R,"R11,R12,R13,R14,R15,R16,R17,R18,R19,R20",R_Axial_DIN0207_L6.3mm_D2.5mm_P10.16mm_Horizontal,,hand solder / plug-in
15,10k,"R21,R22,R23,R24,R25,R26,R27,R28,R29,R30,R42,R47,R48,R49,R50",R_Axial_DIN0207_L6.3mm_D2.5mm_P10.16mm_Horizontal,C2649453,hand solder / plug-in
11,2.2k,"R31,R32,R33,R34,R35,R36,R37,R38,R39,R40,R41",R_Axial_DIN0207_L6.3mm_D2.5mm_P10.16mm_Horizontal,,hand solder / plug-in
4,330R,"R51,R52,R53,R54",R_Axial_DIN0207_L6.3mm_D2.5mm_P10.16mm_Horizontal,,hand solder / plug-in
7,470R,"R55,R56,R57,R58,R59,R60,R61",R_Axial_DIN0207_L6.3mm_D2.5mm_P10.16mm_Horizontal,,hand solder / plug-in
1,2k,R63,R_Axial_DIN0207_L6.3mm_D2.5mm_P10.16mm_Horizontal,,hand solder / plug-in
1,5V 2A module (K7805-2000R3),U1,Converter_DCDC_RECOM_R-78B-2.0_THT,C18212380,hand solder / plug-in
1,PC817,U2,DIP-4_W7.62mm,C20612594,hand solder / plug-in
1,74HC595N,U3,DIP-16_W7.62mm,C507175,hand solder / plug-in

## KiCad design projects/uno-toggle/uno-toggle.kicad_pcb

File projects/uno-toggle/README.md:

# Uno Toggle — start here

**Ordering it:** everything a fab or price calculator asks (size in cm, layers, holes, parts, order-form answers) is in [`MANUFACTURING.md`](MANUFACTURING.md) - generated from the real board, regenerate with `python pipeline.py uno-toggle --only fabreport`.
**Checking the wiring without reading a PCB:** [`CONNECTIONS.md`](CONNECTIONS.md) lists every pin of every part and where it goes, in words.

Two buttons, two LEDs, on an Arduino Uno R3 shield. Press a button → its LED toggles on; press again →
off. Built end-to-end (design → fab → tests → live simulation in the webview) as the second real project
in this workspace, and the first one built entirely with the generalised pipeline.

| I want to... | Read |
|---|---|
| Know what it does and why it's wired this way | `DESIGN_BRIEF.md` |
| Rebuild / change the board | `gen/` — never hand-edit the KiCad files |
| See it in 3D and press its buttons | the webview platform — `python pipeline.py uno-toggle --only webview` |
| Load the firmware | `firmware/uno_toggle.ino` |

## Status — DONE (2026-09-17)
- **Board**: Arduino Uno R3 shield outline (68.58 × 53.34 mm, real chamfered Arduino shape), 2 layers,
  all through-hole, 9 components.
- **Checks**: netlist compare **0 mismatches**, ERC **clean**, DRC **0 errors / 0 unconnected /
  0 schematic-parity issues**. 11 silkscreen warnings remain and are the expected
  value-over-part-outline kind (see `docs/LESSONS_LEARNED.md` lesson 24).
- **Outputs**: `out/fab/` (gerber zip, BOM, CPL), `out/docs/` (STEP, schematic PDF, 3 renders, full BOM).
- **Live simulation**: verified through the platform's API — pressing each button toggles the right LED
  on, and pressing again toggles it off. Real compiled firmware on a real simulated Uno, not a mock.

## Pin map (firmware and board must agree)
| Signal | Uno pin | Part |
|---|---|---|
| BTN1 | D2 | SW1 (+ C1 100nF debounce) |
| BTN2 | D3 | SW2 (+ C2 100nF debounce) |
| LED1 | D8 | R1 330R → D1 (red) |
| LED2 | D9 | R2 330R → D2 (green) |

D0/D1 were avoided (serial) and D13 was avoided (the Uno has its own LED there, which would make
bring-up ambiguous). The 5V rail is deliberately unconnected — nothing on the board draws from it.

## Layout
```
DESIGN_BRIEF.md     spec + the decisions behind it
gen/                netlist.py (single source of truth) + the build scripts
firmware/           uno_toggle.ino - the real sketch
sim/uno/            PlatformIO project; builds the firmware Wokwi actually runs
test/wokwi/         diagram.json + wokwi.toml + USAGE_LOG.md (quota tracking)
lib/                Uno R3 shield symbol + footprint (courtyard stripped, see gen/fix_uno_fp.py)
out/fab, out/docs   manufacturing + documentation outputs
```

## Known cosmetic note
Both LEDs render red in `out/docs/render_*.png` — the 3D model is picked by *footprint*, and both use the
generic `LED_D5.0mm` model. The BOM and schematic correctly say D1 = RED and D2 = GREEN.

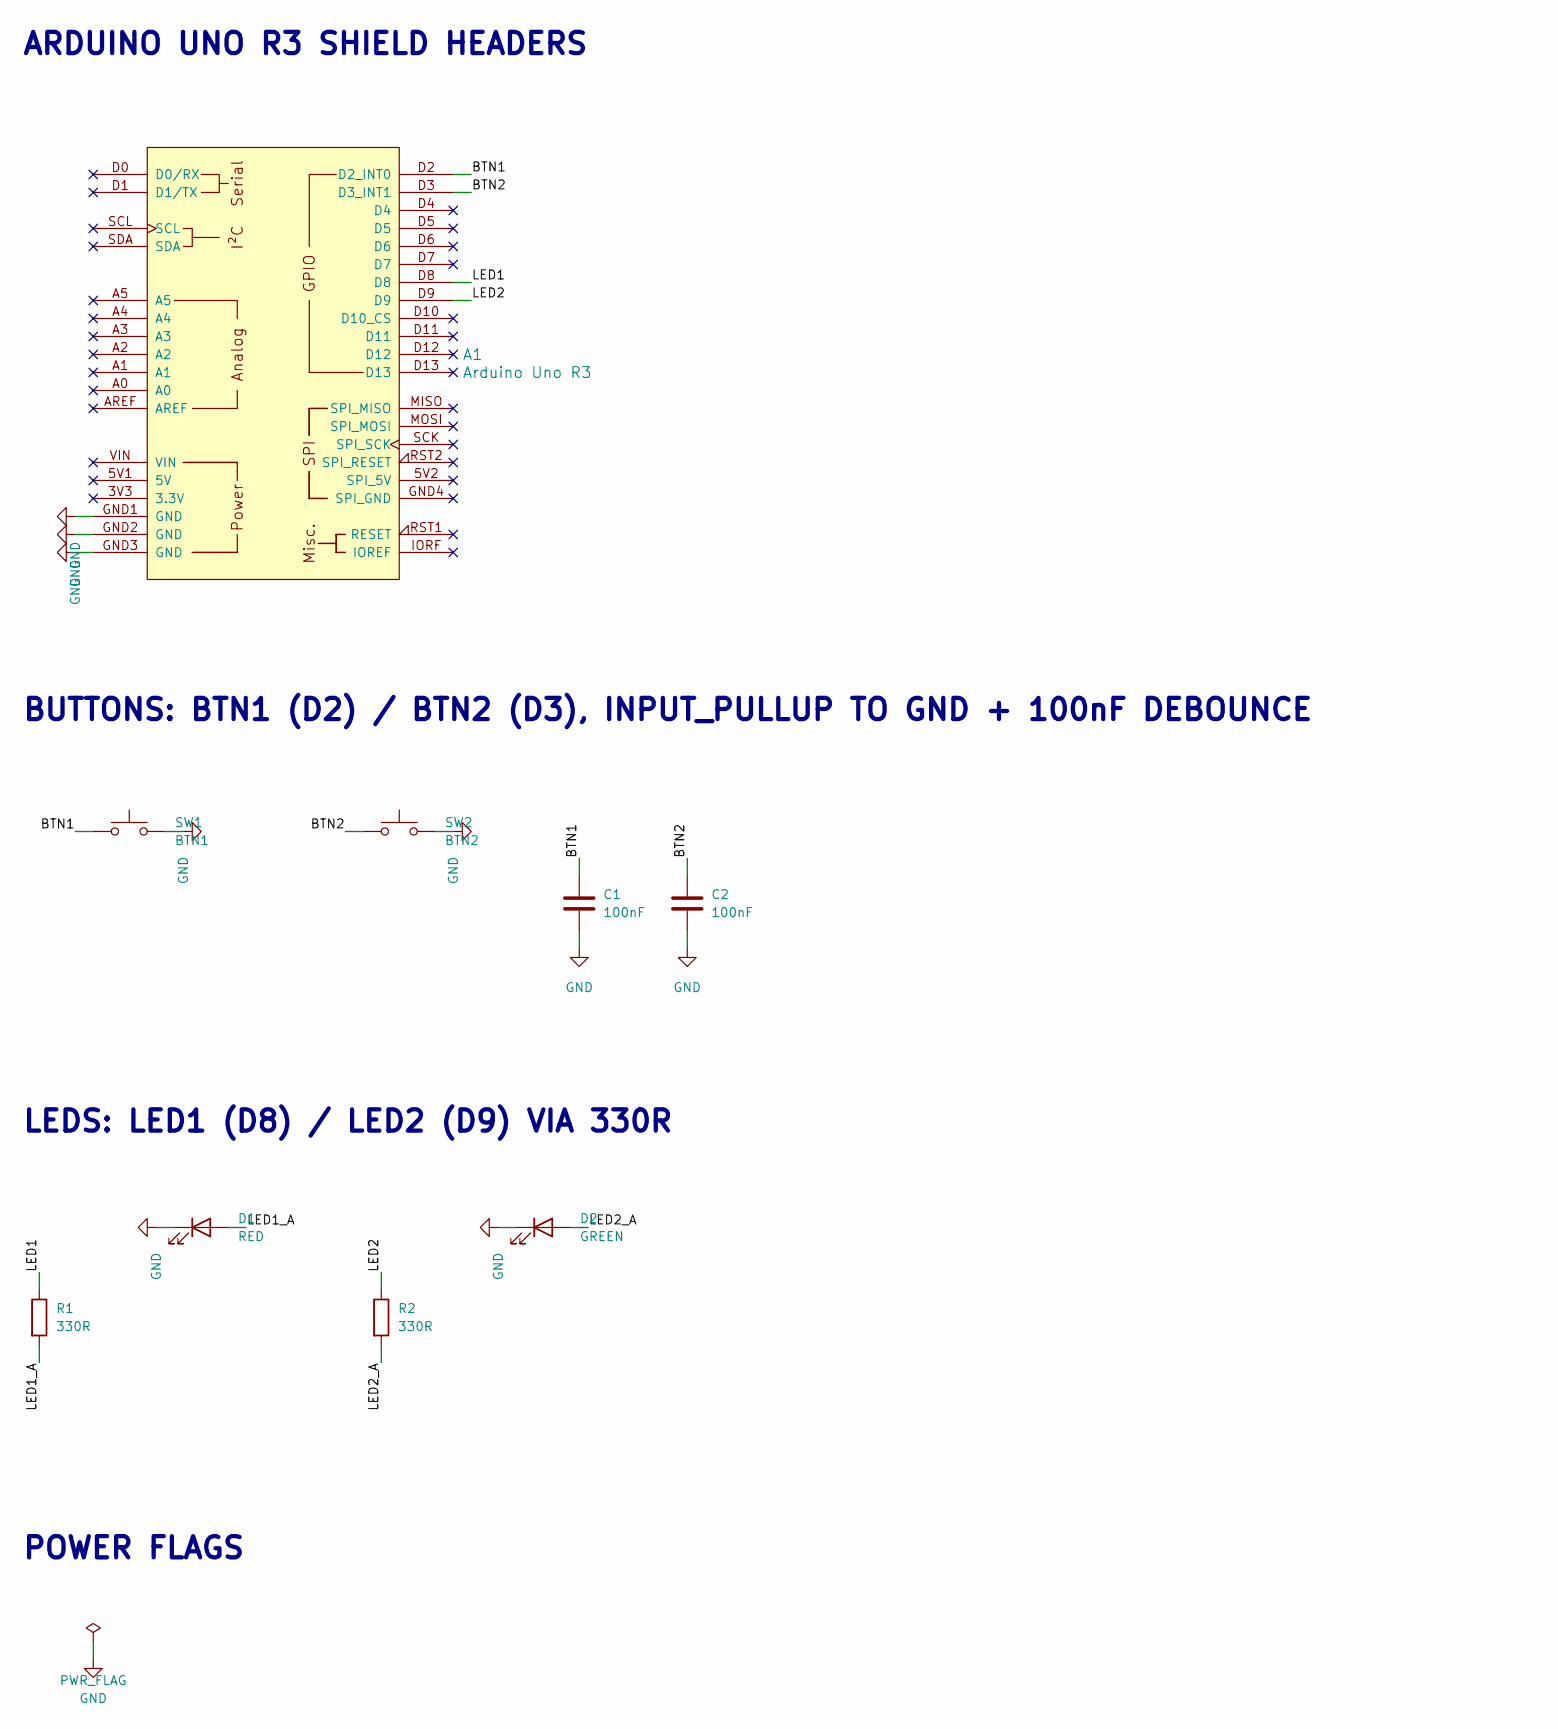
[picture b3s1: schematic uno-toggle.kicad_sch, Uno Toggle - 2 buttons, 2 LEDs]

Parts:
A1: Arduino Uno R3; Arduino_Uno_R3_Shield
C1, C2: 100nF; C_Disc_D5.0mm_W2.5mm_P5.00mm
D1: RED; LED_D5.0mm; LCSC C2895470
D2: GREEN; LED_D5.0mm
R1, R2: 330R; R_Axial_DIN0207_L6.3mm_D2.5mm_P10.16mm_Horizontal
SW1: BTN1; SW_PUSH_6mm
SW2: BTN2; SW_PUSH_6mm

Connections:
/BTN1: A1.D2 (D2_INT0), C1.1, SW1.1
/BTN2: A1.D3 (D3_INT1), C2.1, SW2.1
/LED1: A1.D8, R1.1
/LED1_A: D1.2 (A), R1.2
/LED2: A1.D9, R2.1
/LED2_A: D2.2 (A), R2.2
GND: A1.GND1 (GND), A1.GND2 (GND), A1.GND3 (GND), C1.2, C2.2, D1.1 (K), D2.1 (K), SW1.2, SW2.2

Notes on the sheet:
ARDUINO UNO R3 SHIELD HEADERS
BUTTONS: BTN1 (D2) / BTN2 (D3), INPUT_PULLUP TO GND + 100nF DEBOUNCE
LEDS: LED1 (D8) / LED2 (D9) VIA 330R
POWER FLAGS
